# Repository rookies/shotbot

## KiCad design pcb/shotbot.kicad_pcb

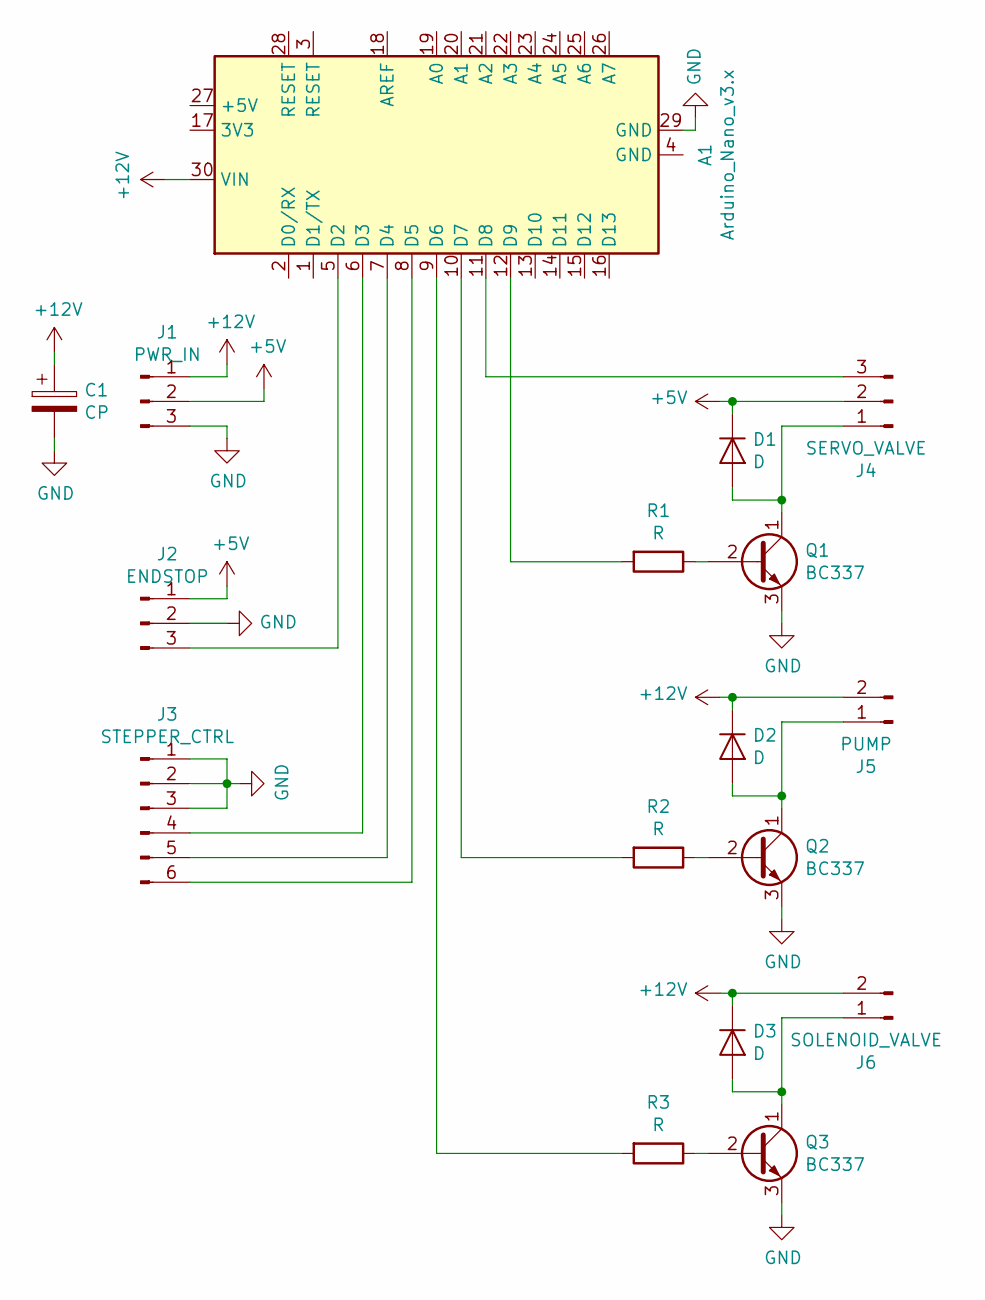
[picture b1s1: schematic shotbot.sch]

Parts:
A1: Arduino_Nano_v3.x; Arduino_Nano
C1: CP; CP_Radial_D8.0mm_P5.00mm
D1, D2, D3: D; D_DO-15_P2.54mm_Vertical_AnodeUp
J1: PWR_IN; PinHeader_1x03_P2.54mm_Vertical
J2: ENDSTOP; PinHeader_1x03_P2.54mm_Vertical
J3: STEPPER_CTRL; PinHeader_1x06_P2.54mm_Vertical
J4: SERVO_VALVE; PinHeader_1x03_P2.54mm_Vertical
J5: PUMP; PinHeader_1x02_P2.54mm_Vertical
J6: SOLENOID_VALVE; PinHeader_1x02_P2.54mm_Vertical
Q1, Q2, Q3: BC337; TO-92_Inline_Wide
R1, R2, R3: R; R_Axial_DIN0207_L6.3mm_D2.5mm_P2.54mm_Vertical

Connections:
+5V: D1.1 (K), J1.2, J2.1, J4.2
+12V: A1.30 (VIN), C1.1, D2.1 (K), D3.1 (K), J1.1, J5.2, J6.2
GND: A1.29 (GND), C1.2, J1.3, J2.2, J3.1, J3.2, J3.3, Q1.3 (E), Q2.3 (E), Q3.3 (E)
unnamed: A1.5 (D2), J2.3
unnamed: A1.6 (D3), J3.4
unnamed: A1.7 (D4), J3.5
unnamed: A1.8 (D5), J3.6
unnamed: A1.9 (D6), R3.2
unnamed: A1.10 (D7), R2.2
unnamed: A1.11 (D8), J4.3
unnamed: A1.12 (D9), R1.2
unnamed: D1.2 (A), J4.1, Q1.1 (C)
unnamed: D2.2 (A), J5.1, Q2.1 (C)
unnamed: D3.2 (A), J6.1, Q3.1 (C)
unnamed: Q1.2 (B), R1.1
unnamed: Q2.2 (B), R2.1
unnamed: Q3.2 (B), R3.1

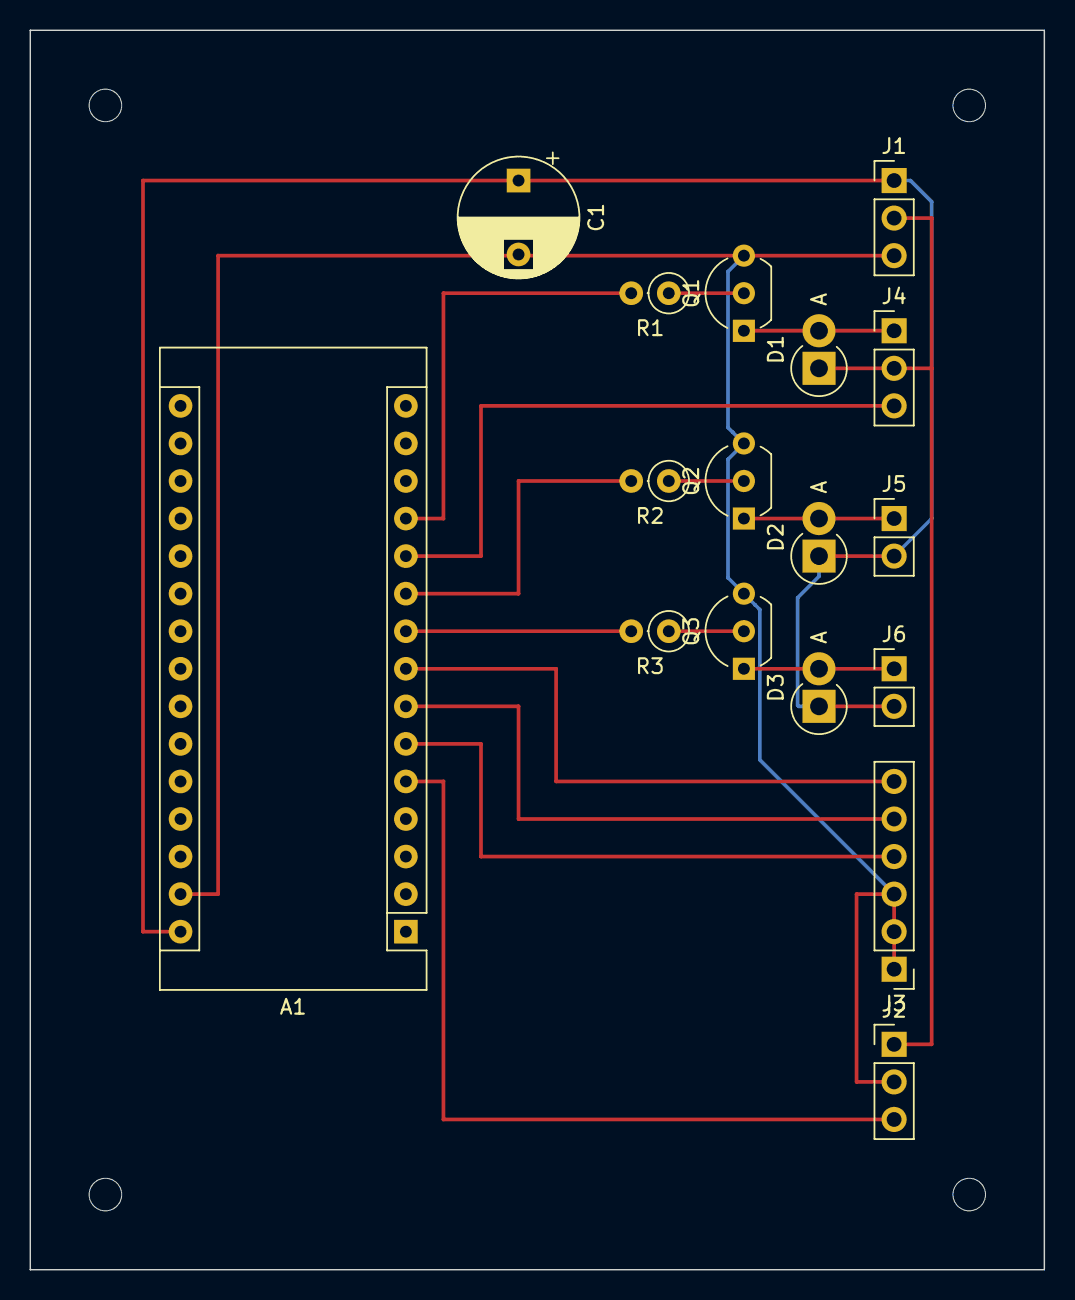
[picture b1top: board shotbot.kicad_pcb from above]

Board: 2 copper layers, 68.6 x 83.8 mm, 17 parts (0 on the bottom side), 17 nets.

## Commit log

2019-09-18 init
2019-09-18 started speech recognition
2019-09-19 implemeted stepper control over serial port
2019-09-19 small fix in serial interface
2019-09-22 suppress posreached for homing
2019-09-22 added endstop released message
2019-09-22 serialtest.py
2019-09-22 disabled auto-homing at startup
2019-09-24 serialtest.py: improved output
2019-09-24 arduino: implemented pump command
2019-09-24 serialtest.py: added pumping
2019-11-02 add elecronics-overview.dia
2019-11-08 add valve control to the software
2019-11-09 add hardware library
2019-11-09 openvalve.py
2019-11-09 add notes
2019-11-09 add solenoid valve to electronics overview
2019-11-12 add solenoid and servo enable pin
2019-11-12 add current state to electronics overview
2019-11-13 add servo library to makefile
2019-11-15 add musictest.py
2019-11-15 use a thread to play music
2019-11-15 serialtest.py: integrate music
2019-11-15 hwcontrol.py: improved logging
2019-11-16 add TaskScheduler
2019-11-16 add task to close servo valve
2019-11-16 add task to switch off valve servo
2019-11-16 add task to close the solenoid valve
2019-11-16 fix function call in TaskScheduler.hh
2019-11-16 add CommandReader
2019-11-16 arduino code cleanup
2019-11-16 clean up arduino config
2019-11-16 implement pumpMaxTime
2019-11-23 enable servo before closing the valve
2019-11-23 arduino code cleanup with new interface
    NOTE: not yet compatible with host software
2019-11-23 fix some problems with new interface
2019-11-23 started rewriting host software
2019-11-23 continue rewriting host software
2019-11-23 implement valve and pump with new interface
2019-11-23 use logger inside hwcontrol.py
2019-11-23 move line classes into protocol.py
2019-11-23 use new hwcontrol in main script
2019-11-28 add CAD models
2019-11-29 change config to six positions
2019-11-29 adapt openvalve.py to new hwcontrol
2019-11-30 add very simple GUI
2019-11-30 solenoid & tablet holder CAD
2019-12-07 add more notes
2020-06-06 ignore gcode, stl, 3mf
2020-06-06 tweak walve and pump time
2020-06-06 recognize.py: try using Google API
2020-06-06 ignore wav
2020-06-06 electronics overview
2020-06-06 dump.txt
2020-06-06 test.py
2020-11-10 add PCB
2021-09-12 Switch to using peristaltic pumps
2021-09-12 Add selector knobs for count and pump
2021-09-12 Show selected count using LEDs
2021-09-12 Make LED color configurable
2021-09-12 Add start button
2021-09-13 Show selected pump using LEDs
2021-09-19 Introduce functions for setting state
2021-09-19 Move pump and stepper into own classes
2021-09-19 Add state machine for serving shots
2021-09-19 Remove TaskScheduler
2021-09-19 Start cleaning up main file
2021-09-28 Switch to new stepper driver
2021-10-14 Add WS2812 holder
2021-10-14 Improve WS2812 holder
2021-10-21 Update used pins
2021-10-22 Add pumpTime config option
2021-10-22 Reverse count LEDs
2021-10-22 Use four pumps
2022-07-09 Add todo
2022-07-09 Add button CAD model
